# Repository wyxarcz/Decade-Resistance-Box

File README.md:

# Decade-Resistance-Box
Decade Resistance Box

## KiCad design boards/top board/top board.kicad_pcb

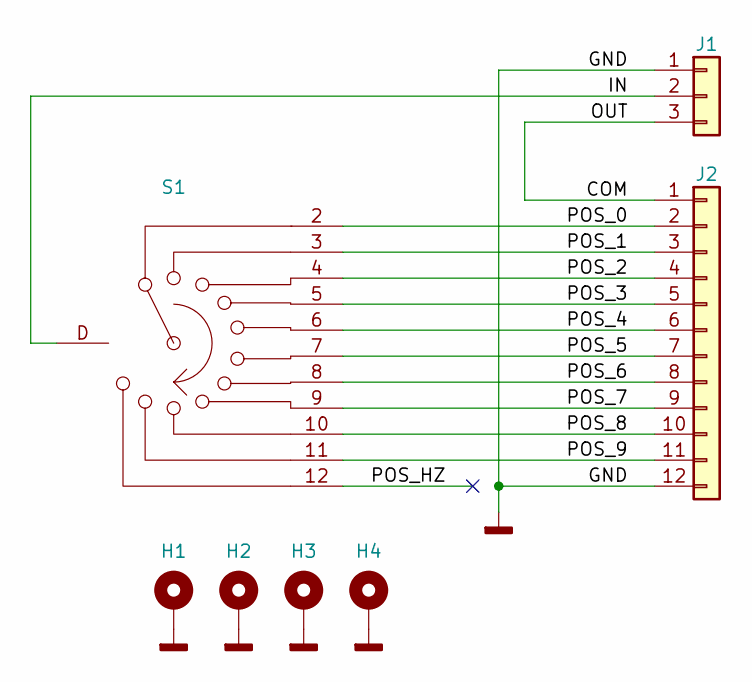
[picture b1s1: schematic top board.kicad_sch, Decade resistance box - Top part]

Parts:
H1, H2, H3, H4: MountingHole_Pad; MountingHole_3.2mm_M3_Pad
J1: Conn_01x03; PinHeader_1x03_P2.54mm_Vertical
J2: Conn_01x12; PinHeader_2x06_P2.54mm_Vertical
S1: RotarySwitch_1P11T

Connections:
/COM: J1.3, J2.1
/IN: J1.2, S1.D
/POS_0: J2.2, S1.2
/POS_1: J2.3, S1.3
/POS_2: J2.4, S1.4
/POS_3: J2.5, S1.5
/POS_4: J2.6, S1.6
/POS_5: J2.7, S1.7
/POS_6: J2.8, S1.8
/POS_7: J2.9, S1.9
/POS_8: J2.10, S1.10
/POS_9: J2.11, S1.11
/POS_HZ: S1.12
GNDD: H1.1 (1_1), H2.1 (1_1), H3.1 (1_1), H4.1 (1_1), J1.1, J2.12

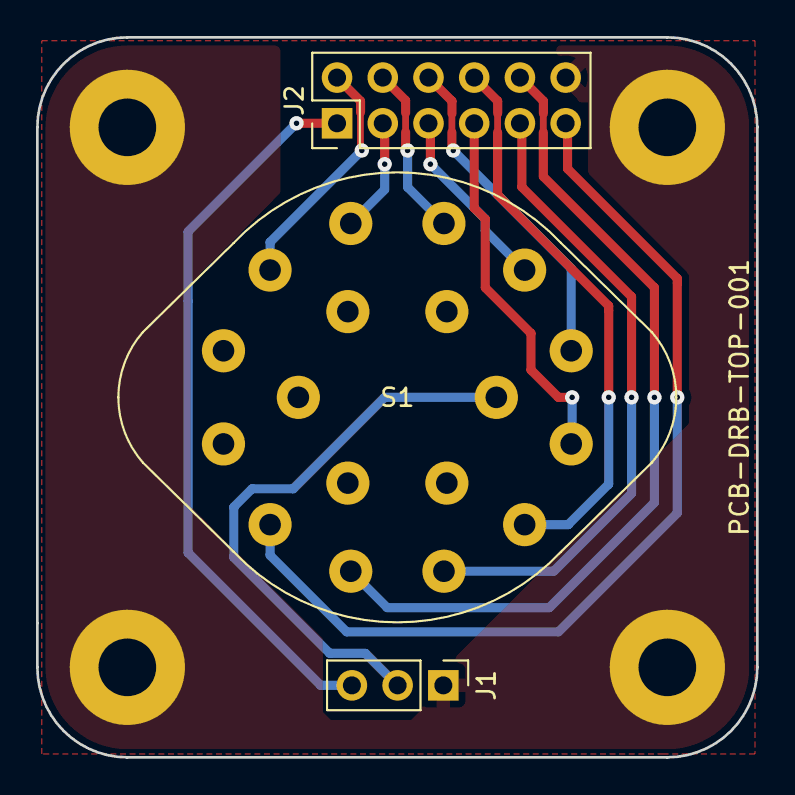
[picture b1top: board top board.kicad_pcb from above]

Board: 2 copper layers, 40.0 x 40.0 mm, 7 parts (0 on the bottom side), 13 nets.

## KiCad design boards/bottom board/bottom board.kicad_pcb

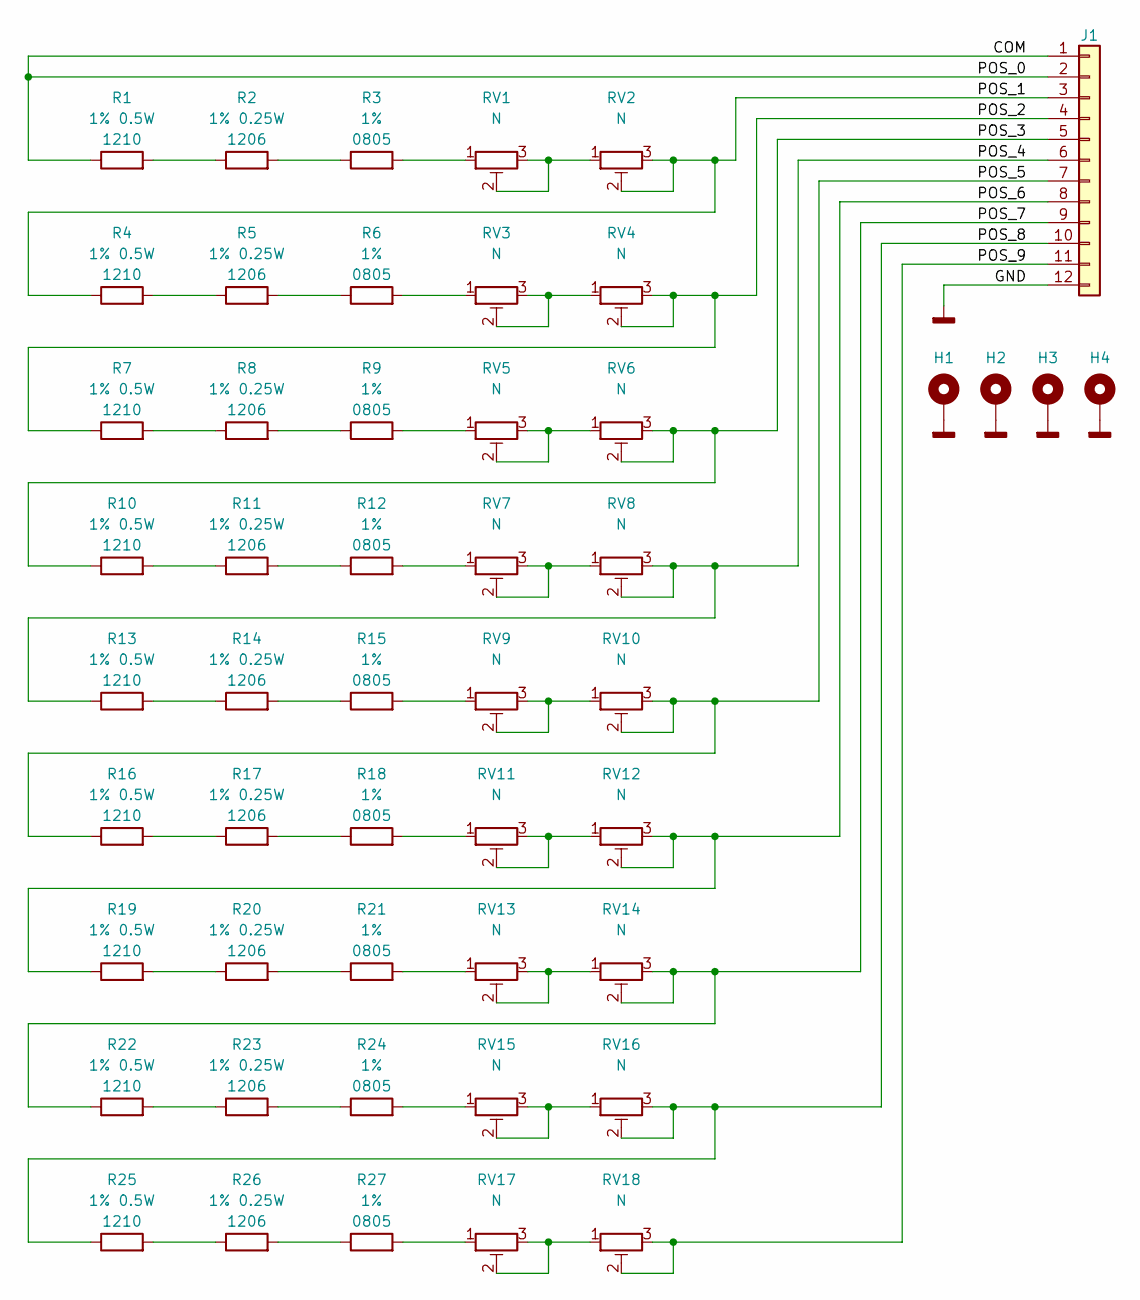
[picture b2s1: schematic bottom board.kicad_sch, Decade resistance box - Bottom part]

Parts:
H1, H2, H3, H4: MountingHole_Pad; MountingHole_3.2mm_M3_Pad
J1: Conn_01x12; PinHeader_2x06_P2.54mm_Vertical
R1, R4, R7, R10, R13, R16, R19, R22, R25: 1% 0.5W; R_1210_3225Metric
R2, R5, R8, R11, R14, R17, R20, R23, R26: 1% 0.25W; R_1206_3216Metric
R3, R6, R9, R12, R15, R18, R21, R24, R27: 1%; R_0805_2012Metric
RV1, RV2, RV3, RV4, RV5, RV6, RV7, RV8, RV9, RV10, RV11, RV12, RV13, RV14, RV15, RV16, RV17, RV18: N; Potentiometer_Bourns_3296W_Vertical

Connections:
/COM: J1.1, J1.2, R1.1
/POS_1: J1.3, R4.1, RV2.2, RV2.3
/POS_2: J1.4, R7.1, RV4.2, RV4.3
/POS_3: J1.5, R10.1, RV6.2, RV6.3
/POS_4: J1.6, R13.1, RV8.2, RV8.3
/POS_5: J1.7, R16.1, RV10.2, RV10.3
/POS_6: J1.8, R19.1, RV12.2, RV12.3
/POS_7: J1.9, R22.1, RV14.2, RV14.3
/POS_8: J1.10, R25.1, RV16.2, RV16.3
/POS_9: J1.11, RV18.2, RV18.3
GNDD: H1.1 (1_1), H2.1 (1_1), H3.1 (1_1), H4.1 (1_1), J1.12
unnamed: R1.2, R2.1
unnamed: R2.2, R3.1
unnamed: R3.2, RV1.1
unnamed: R4.2, R5.1
unnamed: R5.2, R6.1
unnamed: R6.2, RV3.1
unnamed: R7.2, R8.1
unnamed: R8.2, R9.1
unnamed: R9.2, RV5.1
unnamed: R10.2, R11.1
unnamed: R11.2, R12.1
unnamed: R12.2, RV7.1
unnamed: R13.2, R14.1
unnamed: R14.2, R15.1
unnamed: R15.2, RV9.1
unnamed: R16.2, R17.1
unnamed: R17.2, R18.1
unnamed: R18.2, RV11.1
unnamed: R19.2, R20.1
unnamed: R20.2, R21.1
unnamed: R21.2, RV13.1
unnamed: R22.2, R23.1
unnamed: R23.2, R24.1
unnamed: R24.2, RV15.1
unnamed: R25.2, R26.1
unnamed: R26.2, R27.1
unnamed: R27.2, RV17.1
unnamed: RV1.2, RV1.3, RV2.1
unnamed: RV3.2, RV3.3, RV4.1
unnamed: RV5.2, RV5.3, RV6.1
unnamed: RV7.2, RV7.3, RV8.1
unnamed: RV9.2, RV9.3, RV10.1
unnamed: RV11.2, RV11.3, RV12.1
unnamed: RV13.2, RV13.3, RV14.1
unnamed: RV15.2, RV15.3, RV16.1
unnamed: RV17.2, RV17.3, RV18.1

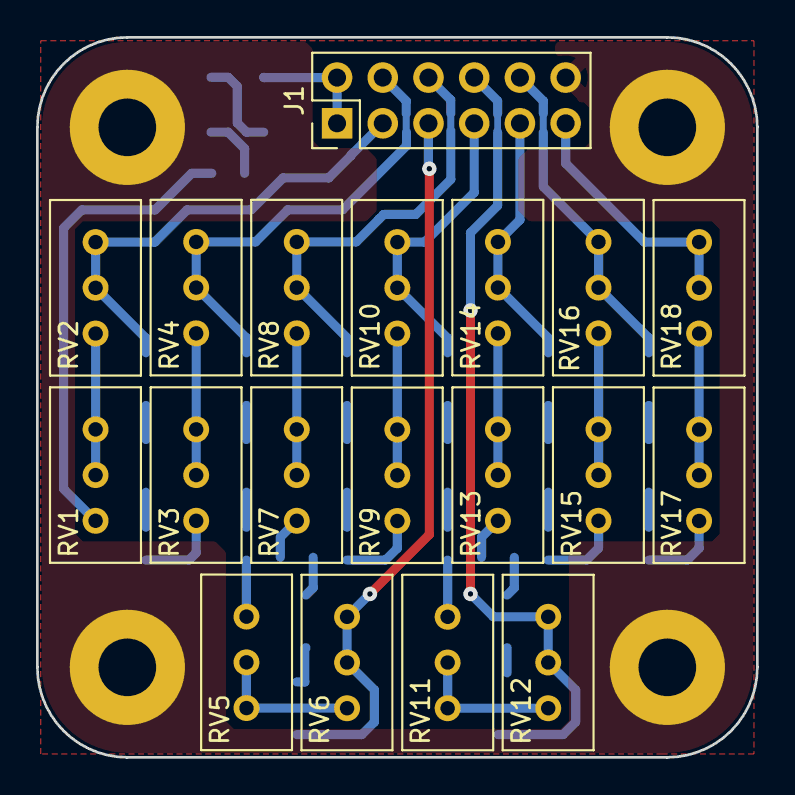
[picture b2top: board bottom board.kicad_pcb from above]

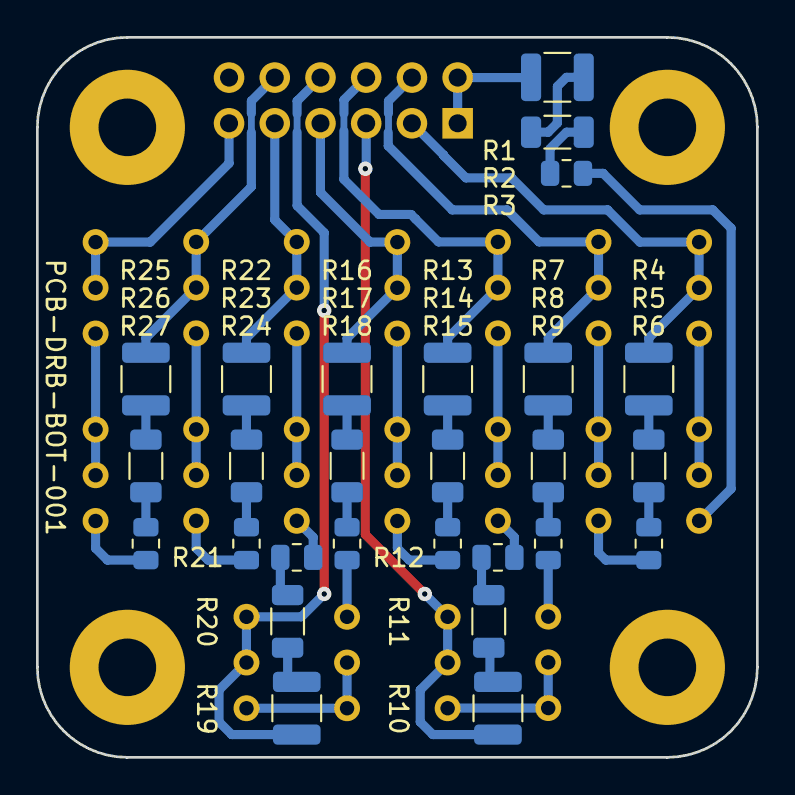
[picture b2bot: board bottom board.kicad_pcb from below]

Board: 2 copper layers, 40.0 x 40.0 mm, 50 parts (27 on the bottom side), 47 nets.
